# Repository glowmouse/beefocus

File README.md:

Beefocus
========

Beefocus is an Open Source Hardware/ Software Telescope Focuser 
The goal of the project is to create a high quality DIY focuser that's
relatively easy to build and modify.

It's similar in spirit to other open source focuser projects.  For
example...

- https://sourceforge.net/projects/arduinoascomfocuserpro2diy/
- http://www.scopefocus.info/arduino-focuser-2
- https://sourceforge.net/projects/arduinomoonlitefocuserclone/?source=directory
- https://github.com/aruangra/PnP-Focus

Why start a new project?
------------------------

- **Originally, I needed a custom focuser solution for my telescope**.
  I have a Celestron C11 with a Hyperstar.  When I started this I
  couldn't find a good out of the box solution.
- **I want to try using an ESP-8266 internet of things micro-controller 
  instead of a traditional arduino**.  I've found that every wire you 
  get rid of simplifies your telescope setup and observing
- **I want to open-source the hardware design under a permissive license.**   
  I'm intrigued by the idea of open-source hardware.  I'm including the
  Eagle CAD files for the hardware under a Creative Commons 4.0 license.
  The goal is to make builds as inexpensive and easy as possible.
- This project is a good personal learning experience.

Code Documentation
------------------

Documentation can be found at https://glowmouse.github.io/beefocus/ 

Status March 2019
-----------------

- I have a physical prototype. It's been field tested and
  it worked almost flawlessly.  The issues that I want to fix before
  "Version 1.0" are tracked on the [Github Project Issues Page].
- The [Prototype ESP8266 Firmware] is posted.  The only thing I want to
  fix in the Firmware is the way you hook up to the Wifi Network.
  Right now you have to modify the Firmware Source Code to add your
  SSID and Password.
- I've published a [Prototype Board Design].  I made my prototype using 
  a CNC circuit router. I had an initial version of the board professionally
  fabricated, and it had a flaw :(.  I'll make a new version of the board
  when I make setting the SSID and Password more user friendly.  I'm also
  waiting for some parts from Ebay.
- There is an INDI Driver for Beefocus, the driver is in the
  [INDI Github Repository] in the [3rd Party Beefocus] directory.
- I've created a [Beefocus INDI Usage] page.

[Github Project Issues Page]:https://github.com/glowmouse/beefocus/issues
[Prototype ESP8266 firmware]: https://github.com/glowmouse/beefocus/tree/master/firmware
[INDI Github Repository]: https://github.com/indilib/indi
[3rd Party Beefocus]: https://github.com/indilib/indi/tree/master/3rdparty/indi-beefocus 
[Prototype board design]: https://github.com/glowmouse/beefocus/tree/master/boards/nema_14_b0
[Beefocus INDI Usage]: https://github.com/glowmouse/beefocus/blob/master/indi_docs/indi_usage_docs.md

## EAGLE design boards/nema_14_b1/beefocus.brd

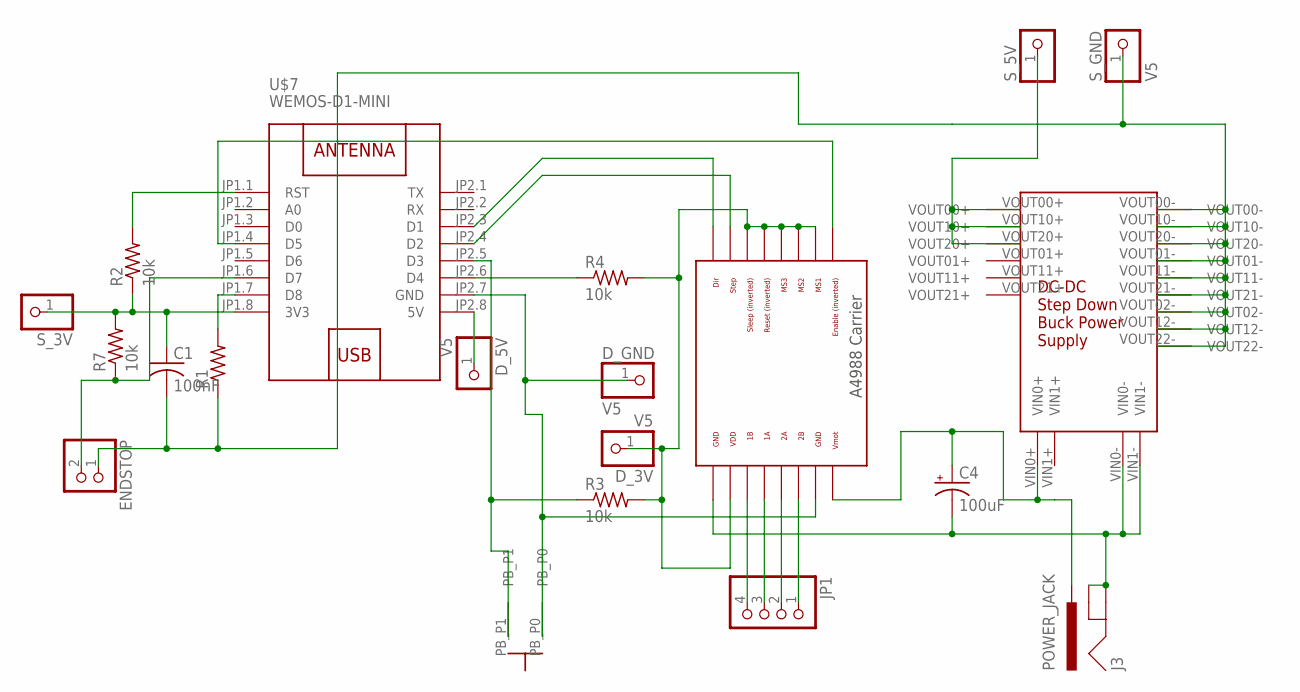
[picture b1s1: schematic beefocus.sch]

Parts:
C1: 100nF; C050-024X044
C4: 100uF; E3,5-8
D_3V, D_5V: V5; 1X01
D_GND: V5; 1X01
ENDSTOP: PINHD-1X2/90; 1X02/90
J3: POWER_JACK; POWER_JACK_PTH
JP1: PINHD-1X4/90; 1X04/90
R1: R-US_0204/7; 0204/7
R2, R4: 10k; 0204/7
R3, R7: 10k; 0309V
S_3V, S_5V: PINHD-1X1; 1X01
S_GND: V5; 1X01
U$1: POLOLU_A4983CARRIER; A4988BREAKOUT
U$6: DCPOWERCONV_R2
U$7: WEMOS-D1-MINI
U$8: BUTTON6X6X10MMSIDE

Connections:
unnamed: C4.-, J3.GND, J3.GNDBREAK, U$1.GND@0 (GND), U$6.VIN0-, U$6.VIN1-
unnamed: D_5V.1, U$7.JP2.8 (5V)
unnamed: U$1.STEP, U$7.JP2.4 (D2)
unnamed: U$1.DIR, U$7.JP2.3 (D1)
unnamed: JP1.1, U$1.2B
unnamed: JP1.2, U$1.2A
unnamed: JP1.3, U$1.1A
unnamed: JP1.4, U$1.1B
unnamed: C4.+, J3.PWR, U$1.VMOT, U$6.VIN0+
unnamed: R3.1, U$7.JP2.5 (D3), U$8.PB_P1
unnamed: U$1.EN, U$7.JP1.4 (D5)
unnamed: R2.2, U$7.JP1.1 (RST)
unnamed: R1.2, U$7.JP1.7 (D8)
unnamed: D_GND.1, U$1.GND, U$7.JP2.7 (GND), U$8.PB_P0
unnamed: D_3V.1, R3.2, R4.2, U$1.MS1, U$1.MS2, U$1.MS3, U$1.RST, U$1.SLP (SLEEP), U$1.VDD
unnamed: ENDSTOP.2, R7.1, U$7.JP1.6 (D7)
unnamed: C1.1, R2.1, R7.2, S_3V.1, U$7.JP1.8 (3V3)
unnamed: R4.1, U$7.JP2.6 (D4)
unnamed: C1.2, ENDSTOP.1, R1.1, S_GND.1, U$6.VOUT00-, U$6.VOUT01-, U$6.VOUT02-, U$6.VOUT10-, U$6.VOUT11-, U$6.VOUT12-, U$6.VOUT20-, U$6.VOUT21-, U$6.VOUT22-
unnamed: S_5V.1, U$6.VOUT00+, U$6.VOUT10+, U$6.VOUT20+

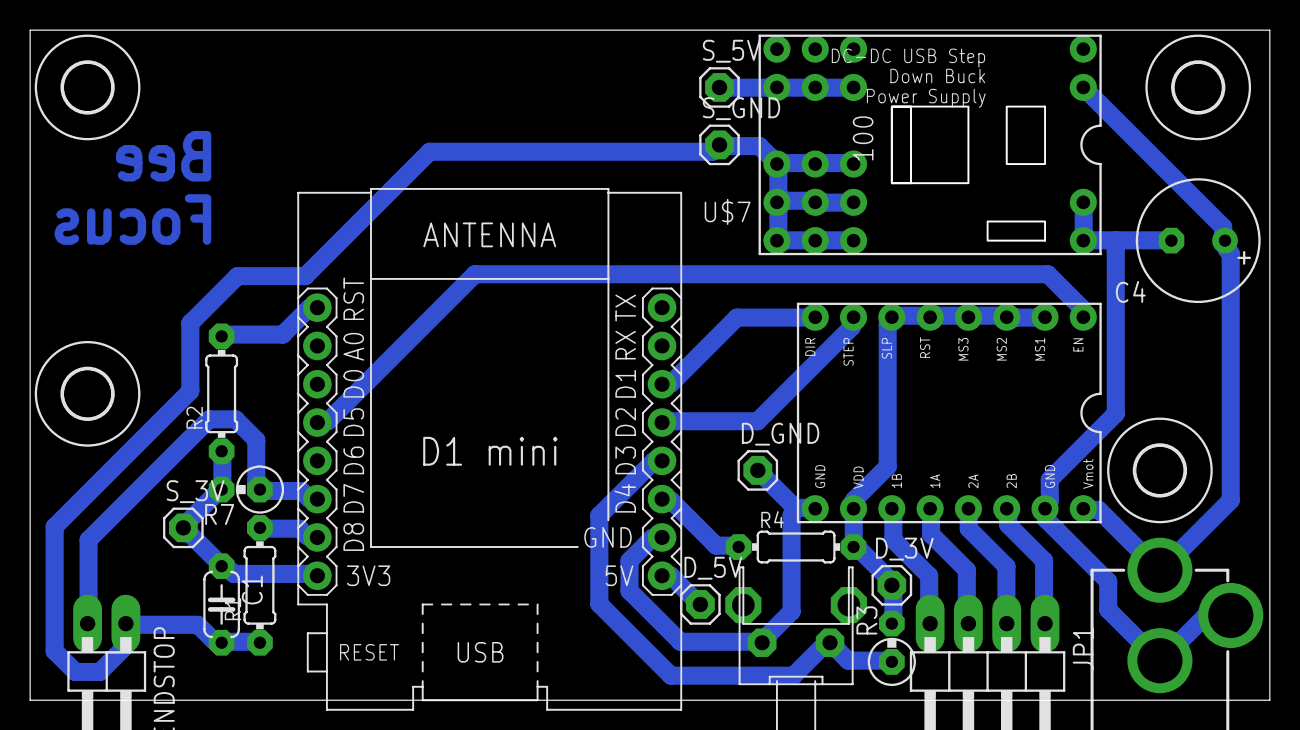
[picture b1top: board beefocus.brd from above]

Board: 2 copper layers, 82.2 x 44.4 mm, 24 parts (0 on the bottom side), 20 nets.

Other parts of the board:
U$2, U$3, U$4, U$5: 3,2

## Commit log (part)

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2018-11-20 - Add the eagle library file for the Wemos IOT board. - Add license and attribution information for the library.
2018-11-20 Add initial version of the firmware
2018-11-20 - Add the sparkfun connectors eagle library that I intend to use in my board design - Add licensing and attribution
2018-11-23 Add eagle libaries under boards Add a sample build under boards
2018-11-23 Remove moved files
2018-11-23 Add pictures of the board and schemantic
2018-11-25 Do not check home / telescode ssid & password into publicly viewable github.
2018-11-25 - Rename the ino file for the focuser so it will compile with the arduino SDC. - Move wifi ssid and password into a separate file - Update the README.md and add a TODO.md
2018-11-25 Fix mark-up
2018-11-25 Fix markdown try 2. TODO, local md browser
2018-11-25 - Firmware change to test sleep mode on the stepper motor controller. - Keeping a stepper motor active draws a lot of current, and for a lot of focuser solutions the focuser won't move if you power d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
2018-11-27 - Added prototype, untested gerber files for the nema 14 board. - Updated TODO. The plan is to migrate the TODO items onto the git hub issue tracker.
2018-11-28 Convert gerber files to RS-274-X format for compatibility with PCB FAB
2018-11-28 Remove TODO.md - everything is migrated to the Issues page in github
2018-12-01 Create a script to download the Arduino SDK
2018-12-02 Check in work on CI to date - will work on feature branch from now on
2018-12-02 Code / warning cleanup, pass 1.
2018-12-02 Remove an argument that's not used and not likely to be used.
2018-12-04 Add an example image of the physical build
2018-12-04 Update README.md to add links to current content.
2018-12-04 Fix broken links, fix spelling mistakes, add periods.
2018-12-06 Proof of concept level CMAKE files and firmwarw simulator.
2018-12-07 Create a start .travis.yml file Create a script to do a basic simulator build
2018-12-07 CI Debug Pass 1
2018-12-07 Fix type-o
2018-12-07 Add C++ 11 directives. C++ 11 isn't on by default in Unbuntu 14.
2018-12-07 Fix a ' mismatch syntax error.
2018-12-07 Add a script to install gtest Modify .travis.yml to allow sudo (for gtest install) and install gtest Rename build script to build-all.sh Open the process_int interface so it can be tested Create a pr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
2018-12-07 Add the script directive back. It looks like travis defaults to ./configure && make && make test
2018-12-08 Remove delays from the hardware interface Refactor focuser_state so it returns the amount of time it waits the caller to wait before it's called again Clean up CMAKE file in unit test directory
2018-12-08 More continous integration / unit test work
    - Made pins a generic enum instead of a build specific enum
    - Added the concept of a debug name to pins
    - Made sure templates for << operators don't confict with std::
    - Unit Test to make sure all pins have names
    - Unit Test to make sure wifi secrets don't get checked in
2018-12-08 Change HardwareInterface class to HWI
    This is a code readability change.
    Before: The step once pin was HardwareInterface::Pin::STEP
    After The step once pin is HWI::Pin::STEP
2018-12-08 Digital writes and reads now use an enum as the argument. This will make it easier to unit test the focuser state module during CI
2018-12-09 Cleanly separate the command parser + unit testing
    - Move status out of the command parser
    - Remove 'deltas' and replace with a 'command packet'
    - Update focuser_state.cpp
    - Add some simple mocks for unit testing
    - Unit test command parser cases
    - Change the simulator so it prints network activity instead of debug logs.
2018-12-09 Pull link from README.md file. I restarted the repository.
2018-12-14 Timed mock of the network interface Test the timed mock of the network interface using check_for_commands
2018-12-14 Use an ENUM type for the pin mode.
2018-12-14 First focuser_state unit test and work on mocking the hardware.
2018-12-15 Refactor the focuser state test so elements that will be common to multiple tests are in separate functions
2018-12-16 Test hardware output against golden results
2018-12-16 Add ABS_POS test to the unit tests Clean up focuser state a bit so it doesn't do as may state transitions
2018-12-16 Filter non-functional debug lines from the unit test output Don't call setup on focuser state in actual arduino code
2018-12-16 Clean up focuser command processing
    - Remove error state from focuser state. It's too hard to reason about.
    - Refactor state_accept_commands so it doesn't always pause 10 seconds after getting a command
    - Reflect the change to state_accept_commands in the focuser_state unit test
    - Separate, more cleanly, the getting of a command from the processing of the command.
2018-12-16 Fix some logic errors exposed in unit testing.
    - Change stepper states to active and inactive, for clarity
    - Stepper now switches from inactive to active and back to do 1 step
    - There is now a 1ms pause when we switch directions
    - Unit tested double forward abs and blacklash rewind the forward.
2018-12-17 Refactor FocuserState for consistency with the rest of the project
    - Rename FocuserState
    - Use num class instead of enum
    - Use an unordered map to get names
2018-12-17 Add Interruptable Flag to Focuser State. All steps are now 1ms
    - Add a "will this command interrupt" flag to the focuser state
    - Make all steps 1ms. It's close to what we already do and saner for testing
    - Move the enum advance into basic_types.h
    - Some other clean-ups
2018-12-17 Focuser State Documentation and Naming Consistency Pass
    - Add comments to the focuser state interface & implementation
    - Rename some functions and variables for consistency
2018-12-18 Focuser State switch to map
    - Redo the focuser state switch as an unordered map
    - Add a unit test to make sure all states have implementations
2018-12-18 Basic unit test for Home command
    - Rename hardware output events to just hardware events
    - Mock hardware input events
    - Create a simple unit test that homes the focuser
2018-12-18 Fix travis CI issue.
2018-12-19 Interface Cleanup and Unit Testing Documentation
    - Removed the reset from the net interface
    - Removed the extra simple net interfaces. Everything can be done using
    the timed interface
    - Documented events and cleaned up some of the interface for events.
2018-12-21 Move event testing mocks into its own file
2018-12-21 Move debug test mock out of test_mocks.h and into its own file
2018-12-21 Move net test mocks into separate header
2018-12-21 Move test mocks for hardware into a new file
2018-12-21 Document test_mock_debug and test_mock_hardware
2018-12-21 Make input events const on the net interface.
2018-12-21 Documment the net interface mock & clean-up
    - Document the net interface mock
    - Remove the comment filter from the net interface mock - it's not core
    functionality
    - Put includes in alphabetical order
2018-12-21 Scripts to run doxygen and deploy to github.
2018-12-21 Add doxygen link to README.md
2018-12-21 Create view script. Readme.md is now the mainpage for Doxygen.
2018-12-21 Deploy code docs to GitHub pages
2018-12-21 Report startus while moving, tests, clean up commands
    - Add ability to check for status more often while moving
    - Unit test pstatus and sstatus
    - Remove status from command set
    - Remove ping from command set
2018-12-21 Create a Home Status command and test
    - Create a command for figuring out of the focuser is homed
    - Add test coverage in unit testing
2018-12-21 Fix Arduino warnings
2018-12-22 Remove sleep and wake commands for simplification. Test interruptions.
    - Remove sleep and wake. The caller shouldn't have to set this state.
    - Fix and test move interrupions.
2018-12-22 More interrupt while blank implementation and testing.
2018-12-22 Tests for home interruptions and implementation.
2018-12-22 Fix bug in backlash correction interrupts. Refactor focuser stack. Warnings.
    - Fixed a bug in the backlash correction interrupt code.
    - Test backlash correction interrupts
    - Refactored the focuser stack to hide vector implementation.
    - Fix warnings
2018-12-22 Rename COMMAND_PACKET. Hide & Simplify implementation.
2018-12-22 Start breaking part FocuserState to improve modulariy
2018-12-22 More more code out of the Focuser class
2018-12-22 Documentation and clean-up
2018-12-22 Begin making state argumement more typesafe.
2018-12-22 More Focuser State Argument type safety
2018-12-22 Add the concept of timing parameters to the focuser state.
2018-12-22 Focuser state can tell time. checkForCommands only triggers on epochs
2018-12-22 Focuser enters and leaves sleep state + unit testing.
2018-12-23 Fix compiler warning
2018-12-23 Bug fixes from board testing
    - Use Delay() where possible. I suspect DelayMicroseconds doesn't service the Wifi
    - Turn off writing the wifi configuration to flash
    - Add a maximum stack-size guard to the focuser state-stack.
2018-12-23 Board Power Testing + Fix Home Bug
2019-01-05 Add the concept of builds to the firmware.
2019-01-05 Implement ignore home command build param and test
2019-01-05 Update board to fix lost trace to ground :(
2019-01-05 Change sstatus to mstatus.
2019-01-05 Change hstatus to sstatus (sync status)
2019-01-05 Renaming pass.
2019-01-05 Add sync command to focuser state.
2019-01-05 Add params to the actual (esp8266) focuser.
2019-01-05 Name fixing in code and comments.
2019-02-02 Add firmware version and caps to the firmware.
2019-02-02 Stop focuser from going beyound the max abosolute position in the caps
2019-02-02 Opps, wrong max position for my build
2019-02-08 clang warnings fixes
2019-02-17 Create a lazy home command + unit test
2019-02-18 Relative Move command + unit tests.
2019-02-28 Initial INDI documentation + screen shots.
2019-02-28 Add more basic usage documentation
2019-02-28 Fix image links
2019-02-28 Sync sync text with image.
2019-03-03 Minor doc updates
2019-03-03 Add more tabs to documentation
2019-03-03 Add button number examples
2019-03-03 Fix formatting error
2019-03-03 Add ethernet connection
2019-03-18 Update readme with current status
2019-03-26 Wifi configuration page - initial work
2019-03-26 Fix javascript for SSID text button - now displays text content.
2019-03-26 Remove preview configuration, text updates in configuration.html now propegate to all views.
2019-03-26 Wifi port now goes through one group, and refreshed to all other groups.
2019-03-26 Password now reflects on global and echos to hidden fields
2019-03-27 Refactoring inputs and storing values
2019-03-31 Update board to take a push button switch. This will be used to do a hard reset in the future
2019-04-13 Change microstepping to 1/16th on board.
2019-04-13 Revised gerber files
2019-05-03 Firmware web page development. Work in progress.
2019-05-03 Clang build + clang warnings fixes (including one functional bug in the Unit Tests).
2019-05-26 Start another circuit board variant.
2019-05-31 Modifications so the gerber files are acceptable to allpcb.com
2019-06-14 Documentation pass for focuser_state. Also moved some of the constants into the private section of the class.
2019-06-21 Start of work to use a boost::stream like interface for network connections
2019-06-22 Clen up IO streaming interfaces.
2019-06-22 Add command to shut down debug output. Create a new board profile for micro-stepping boards.
2019-06-23 Fix timeouts while writing IO
    - Add the concept of a flush to the output streams
    - Buffer output until flush (or the buffer becomes full)
    - Set no delay writes
    - Turn off wifi power saving mode until the write buffer is clear
2019-06-23 Add concept of hostname
2019-06-28 Revert light wifi sleep mode for now - causes unreliable connections
2019-07-11 Fix clang warnings
2019-07-12 Fix a bug that caused output to default to const std::string& operator when const char* was desired.
2020-01-02 - Switch unique_ptrs to shared_pointers - Some minor interface cleanup.

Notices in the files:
parts and their libraries:
SparkFun-Connectors: Licensing: Creative Commons ShareAlike 4.0 International - https://creativecommons.org/licenses/by-sa/4.0
diy-modules: Released under the Creative Commons Attribution 4.0 International License: http://creativecommons.org/licenses/by/4.0
